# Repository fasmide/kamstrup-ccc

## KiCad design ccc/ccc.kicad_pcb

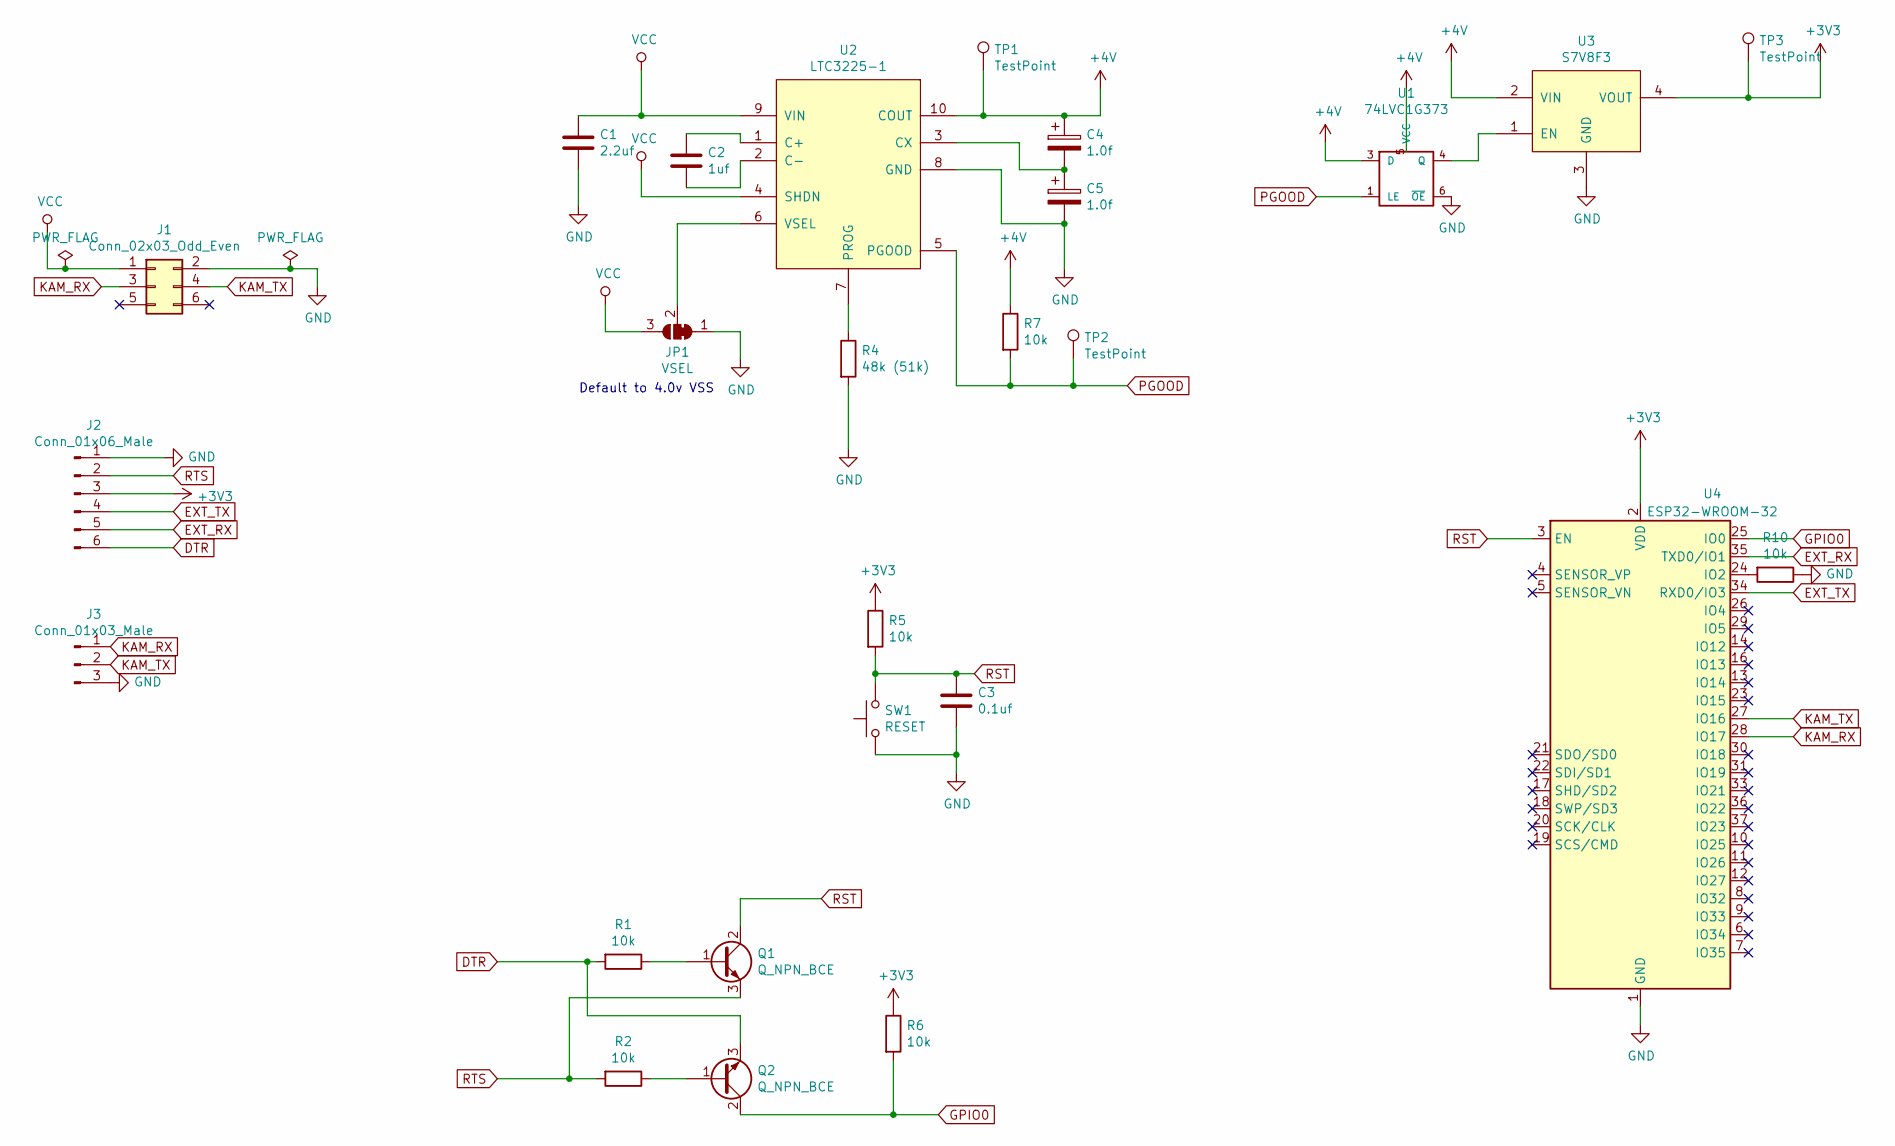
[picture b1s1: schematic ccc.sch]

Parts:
C1: 2.2uf; C_1206_3216Metric_Pad1.42x1.75mm_HandSolder
C2: 1uf; C_1206_3216Metric_Pad1.42x1.75mm_HandSolder
C3: 0.1uf; C_1206_3216Metric_Pad1.42x1.75mm_HandSolder
C4, C5: 1.0f; C_Radial_D10.0mm_H12.5mm_P5.00mm
J1: Conn_02x03_Odd_Even; PinSocket_2x03_P2.54mm_Horizontal
J2: Conn_01x06_Male; PinHeader_1x06_P2.54mm_Horizontal
J3: Conn_01x03_Male; PinHeader_1x03_P2.54mm_Horizontal
JP1: VSEL; SolderJumper-3_P1.3mm_Bridged12_RoundedPad1.0x1.5mm
Q1, Q2: Q_NPN_BCE; SOT-23
R1, R2, R5, R6, R7, R10: 10k; R_0805_2012Metric
R4: 48k (51k); R_0805_2012Metric
SW1: RESET; SW_Tactile_SPST_Angled_PTS645Vx39-2LFS
TP1, TP2, TP3: TestPoint; TestPoint_Pad_D2.5mm
U1: 74LVC1G373; SOT-23-6_Handsoldering
U2: LTC3225-1; DFN-10-1EP_2x3mm_P0.5mm_EP0.64x2.4mm
U3: S7V8F3; PinHeader_1x04_P2.54mm_Vertical
U4: ESP32-WROOM-32

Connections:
+3V3: J2.3, R5.1, R6.1, TP3.1, U3.4 (VOUT), U4.2 (VDD)
+4V: C4.1, R7.1, TP1.1, U1.3 (D), U1.5 (VCC), U2.10 (COUT), U3.2 (VIN)
DTR: J2.6, Q2.3 (E), R1.2
EXT_RX: J2.5, U4.35 (TXD0/IO1)
EXT_TX: J2.4, U4.34 (RXD0/IO3)
GND: C1.2, C3.2, C5.2, J1.2, J2.1, J3.3, JP1.1 (A), R4.2, R10.1, SW1.1, U1.2 (GND), U1.6 (~OE), U2.8 (GND), U3.3 (GND), U4.1 (GND), U4.15 (GND), U4.38 (GND)
GPIO0: Q2.2 (C), R6.2, U4.25 (IO0)
KAM_RX: J1.3, J3.1, U4.28 (IO17)
KAM_TX: J1.4, J3.2, U4.27 (IO16)
unnamed: C2.1, U2.1 (C+)
unnamed: C2.2, U2.2 (C-)
unnamed: C4.2, C5.1, U2.3 (CX)
unnamed: JP1.2 (C), U2.6 (VSEL)
unnamed: Q1.1 (B), R1.1
unnamed: Q2.1 (B), R2.1
unnamed: R4.1, U2.7 (PROG)
unnamed: R10.2, U4.24 (IO2)
unnamed: U1.4 (Q), U3.1 (EN)
PGOOD: R7.2, TP2.1, U1.1 (LE), U2.5 (PGOOD)
RST: C3.1, Q1.2 (C), R5.2, SW1.2, U4.3 (EN)
RTS: J2.2, Q1.3 (E), R2.2
VCC: C1.1, J1.1, JP1.3 (B), U2.4 (SHDN), U2.9 (VIN)

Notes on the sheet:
Default to 4.0v VSS

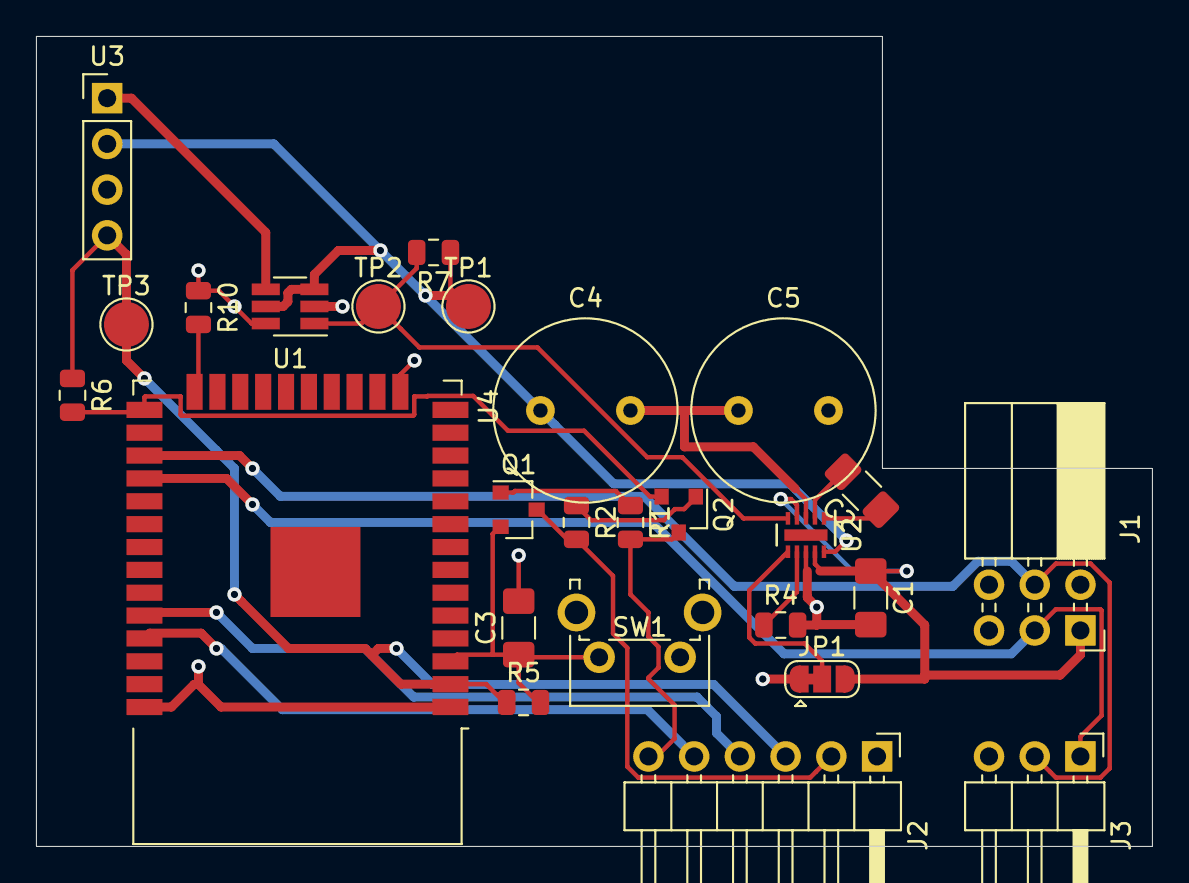
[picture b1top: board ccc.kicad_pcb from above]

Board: 2 copper layers, 62.0 x 45.0 mm, 26 parts (0 on the bottom side), 22 nets.

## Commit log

2019-05-16 Some what prototype with esp8266 which cannot be programmed
2019-05-16 Added cp2102n datasheet
2019-05-19 Added usb to uart bridge
2019-05-23 usb bridge readability update
2019-05-23 Removed usb bridge - added programming header
2019-05-24 Added various testpoints and moved some autoprogramming logic resistors
2019-05-24 Assigned footprints for stuff
2019-05-28 esp8266 is now removed from the schematic - some charging layout done
2019-06-06 Added S7V8F3 regulator to library
2019-06-06 Added flipflop - did some layout
2019-06-13 Fully wired - needs some finish here and there
2019-06-21 New schematic pdf
